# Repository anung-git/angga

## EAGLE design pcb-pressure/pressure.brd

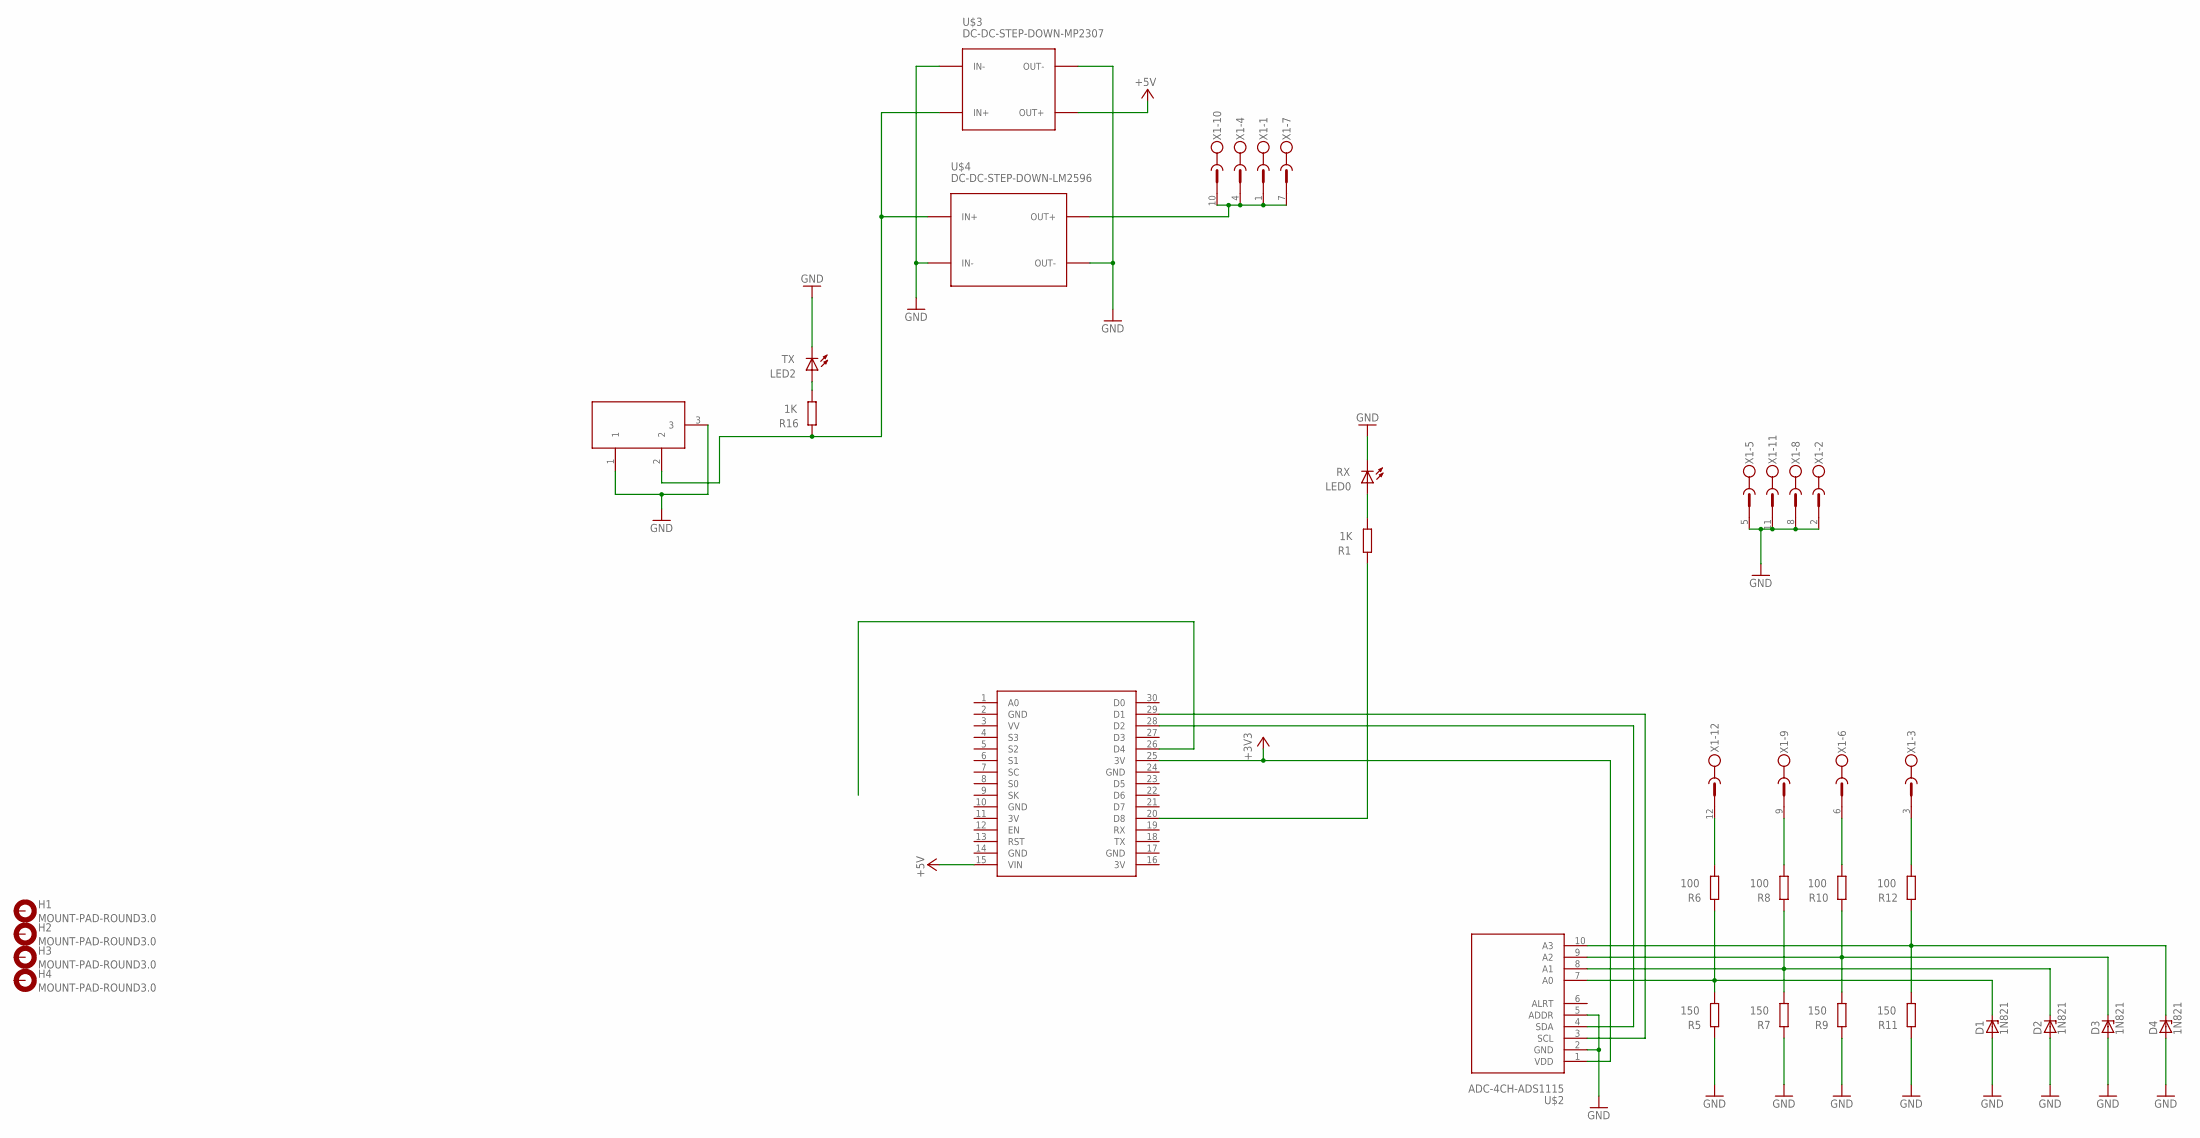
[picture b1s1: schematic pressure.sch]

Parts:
D1, D2, D3, D4: 1N821; DO35Z10
DC1: DC21MMX; DC-21MM
H1, H2, H3, H4: MOUNT-PAD-ROUND3.0; 3,0-PAD
LED0: RX; LED5MM
LED2: TX; LED5MM
R1, R16: 1K; 0207/10
R5, R7, R9, R11: 150; 0207/10
R6, R8, R10, R12: 100; 0207/10
U$1: NODEMCU
U$2: ADC-4CH-ADS1115
U$3: DC-DC-STEP-DOWN-MP2307
U$4: DC-DC-STEP-DOWN-LM2596
X1: MSTBV12

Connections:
3V: U$1.11 (3V), U$1.16 (3V)
+3V3: U$1.25 (3V), U$2.1 (VDD)
+5V: U$1.15 (VIN), U$3.OUT+
GND: D1.A, D2.A, D3.A, D4.A, DC1.1, DC1.3, LED0.K (C), LED2.K (C), R5.2, R7.2, R9.2, R11.2, U$1.2 (GND), U$1.10 (GND), U$1.14 (GND), U$1.17 (GND), U$1.24 (GND), U$2.2 (GND), U$2.5 (ADDR), U$3.IN-, U$3.OUT-, U$4.IN-, U$4.OUT-, X1.2, X1.5, X1.8, X1.11
unnamed: DC1.2, R16.2, U$3.IN+, U$4.IN+
unnamed: U$4.OUT+, X1.1, X1.4, X1.7, X1.10
unnamed: D1.C, R5.1, R6.2, U$2.7 (A0)
unnamed: D2.C, R7.1, R8.2, U$2.8 (A1)
unnamed: D3.C, R9.1, R10.2, U$2.9 (A2)
unnamed: R1.2, U$1.20 (D8)
unnamed: D4.C, R11.1, R12.2, U$2.10 (A3)
unnamed: R6.1, X1.12
unnamed: R8.1, X1.9
unnamed: R10.1, X1.6
unnamed: LED2.A, R16.1
unnamed: R12.1, X1.3
unnamed: U$1.29 (D1), U$2.3 (SCL)
unnamed: U$1.28 (D2), U$2.4 (SDA)
unnamed: LED0.A, R1.1

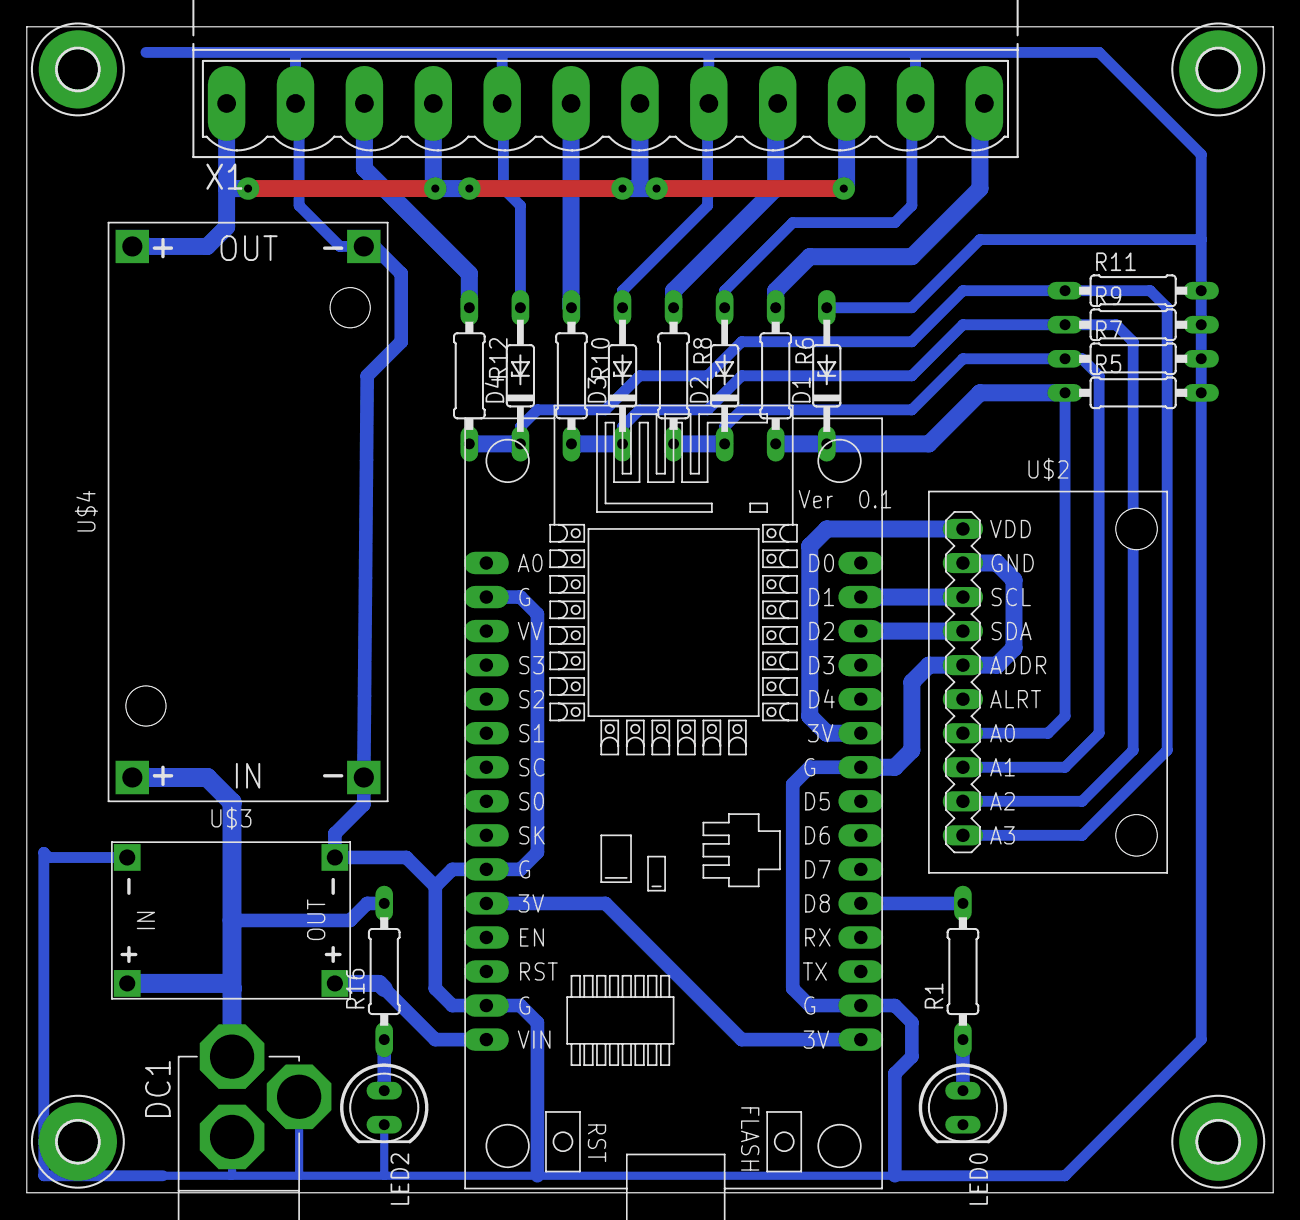
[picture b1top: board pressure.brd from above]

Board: 2 copper layers, 93.0 x 87.0 mm, 26 parts (0 on the bottom side), 19 nets.

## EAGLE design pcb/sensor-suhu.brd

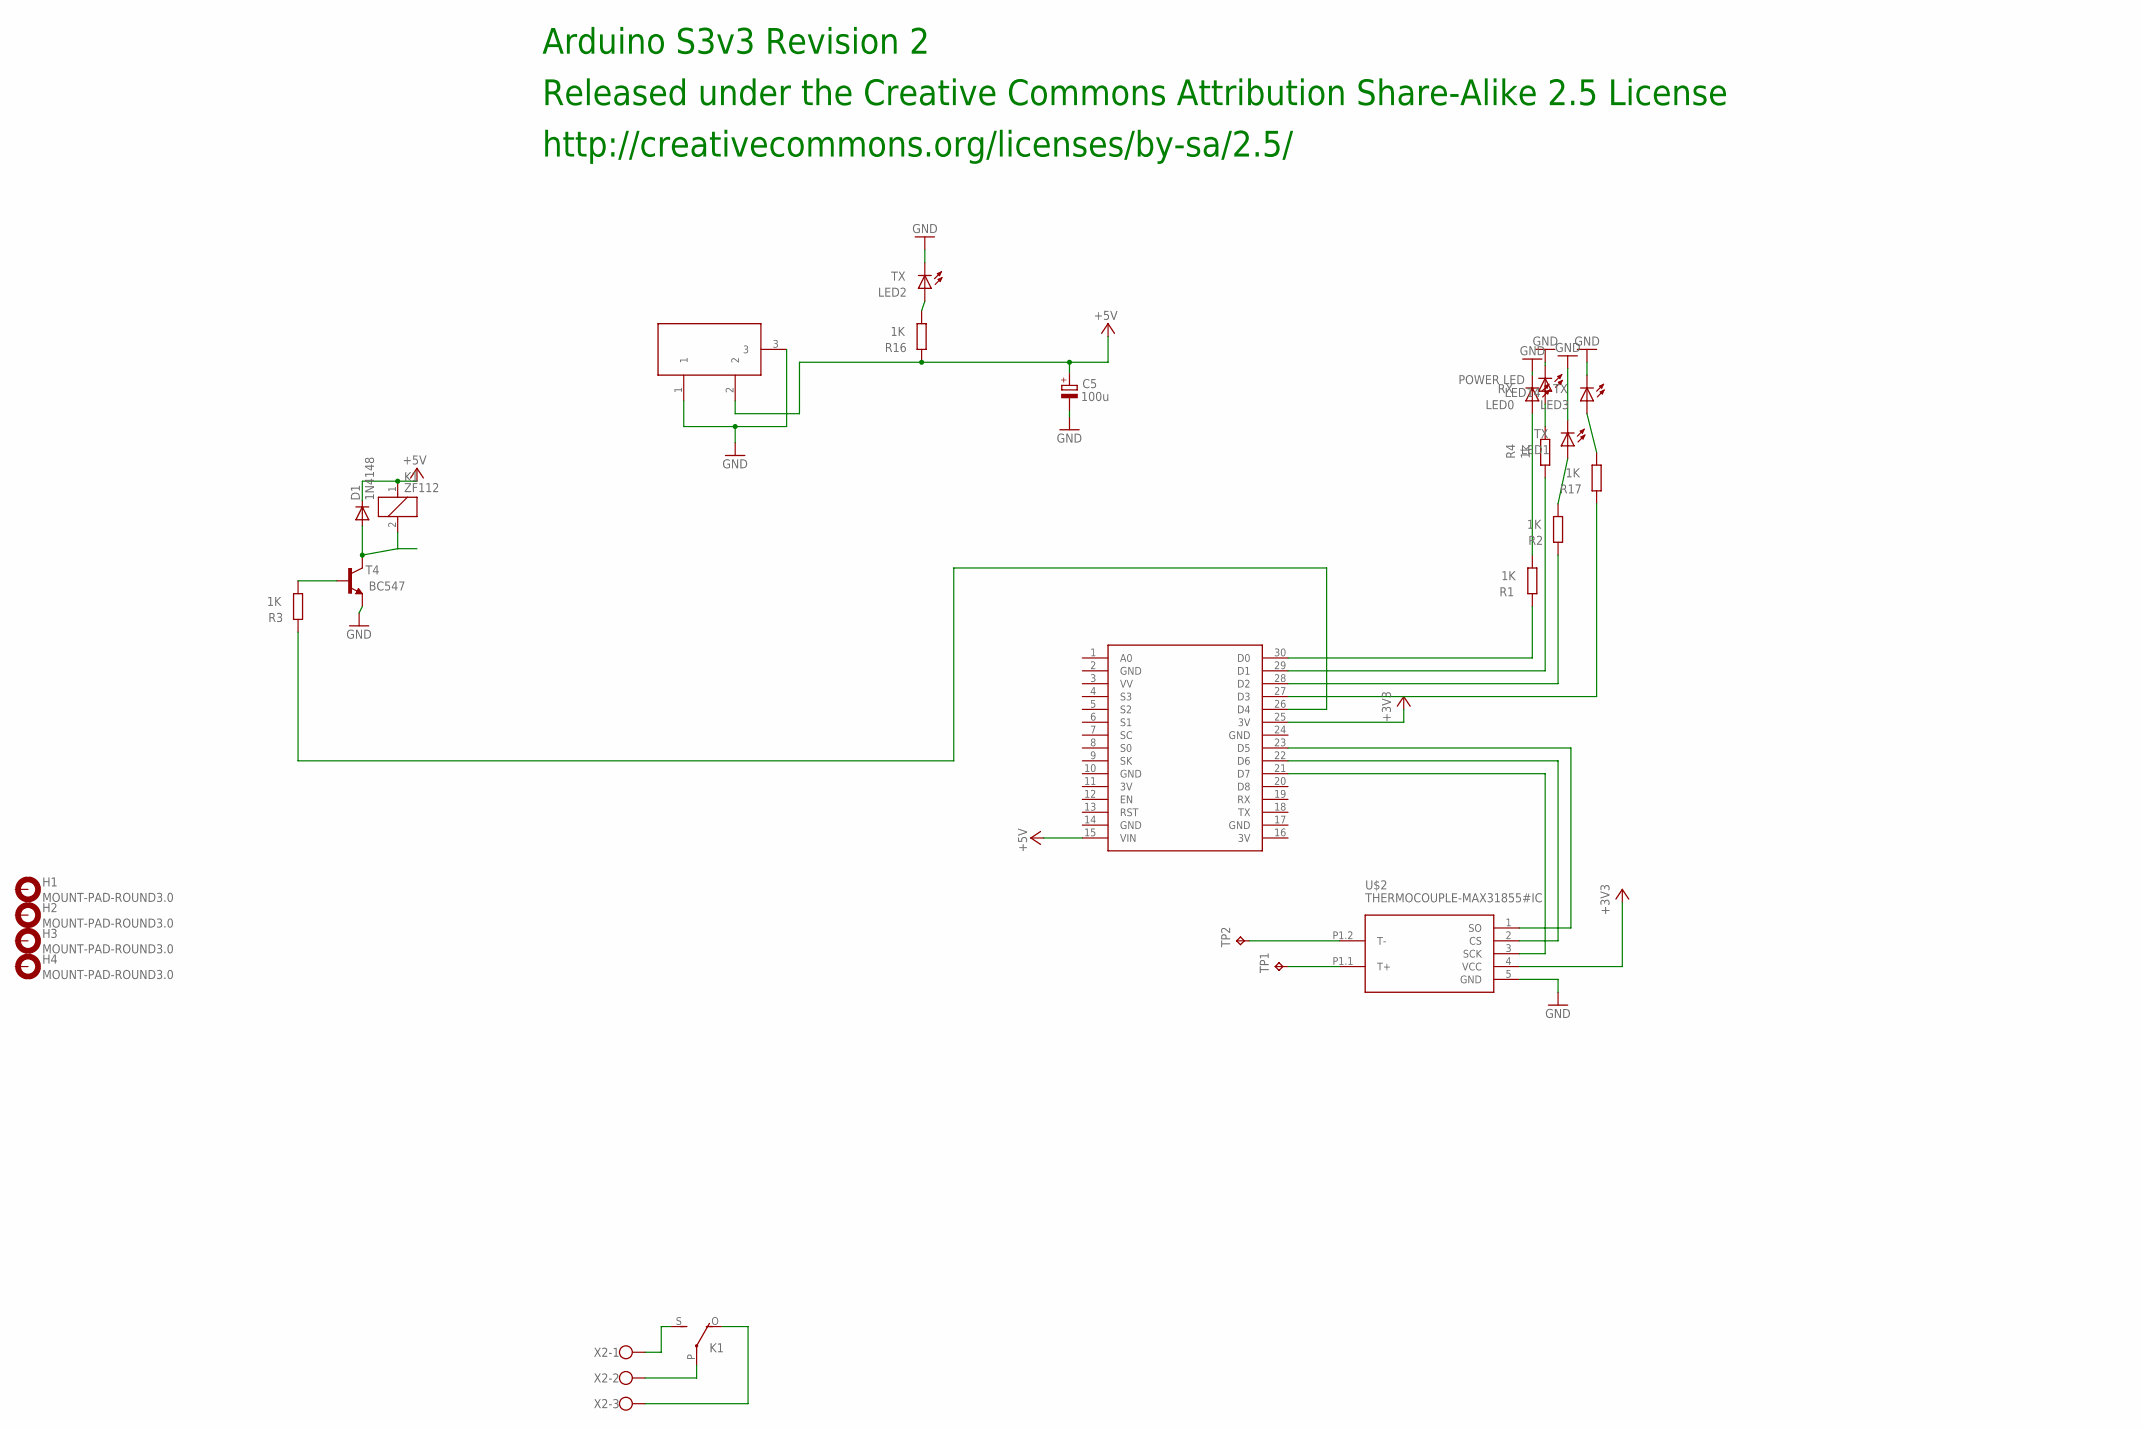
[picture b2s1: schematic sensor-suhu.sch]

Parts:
C5: 100u; E3,5-8
D1: 1N4148; DO35-10
DC1: DC21MMX; DC-21MM
H1, H2, H3, H4: MOUNT-PAD-ROUND3.0; 3,0-PAD
K1: ZF112
LED0: RX; LED5MM
LED1, LED2, LED3: TX; LED5MM
LED14: POWER LED; LED5MM
R1, R2, R3, R16, R17: 1K; 0207/10
R4: 1k; 0207/10
T4: BC547; TO92
TP1, TP2: TPPAD1-17Y; P1-17Y
U$1: NODEMCU
U$2: THERMOCOUPLE-MAX31855#IC
X2: W237-103

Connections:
3V: U$1.11 (3V), U$1.16 (3V)
+3V3: U$1.25 (3V), U$2.4 (VCC)
+5V: C5.+, D1.C, DC1.2, K1.1, R16.2, U$1.15 (VIN)
GND: C5.-, DC1.1, DC1.3, LED0.K (C), LED1.K (C), LED2.K (C), LED3.K (C), LED14.K (C), T4.1 (E), U$1.2 (GND), U$1.10 (GND), U$1.14 (GND), U$1.17 (GND), U$1.24 (GND), U$2.5 (GND)
unnamed: R3.1, T4.2 (B)
unnamed: K1.O, X2.3
unnamed: LED14.A, R4.1
unnamed: D1.A, K1.2, T4.3 (C)
unnamed: U$1.23 (D5), U$2.1 (SO)
unnamed: U$1.22 (D6), U$2.2 (CS)
unnamed: U$1.21 (D7), U$2.3 (SCK)
unnamed: K1.S, X2.1
unnamed: K1.P, X2.2
unnamed: R1.2, U$1.30 (D0)
unnamed: R4.2, U$1.29 (D1)
unnamed: R2.2, U$1.28 (D2)
unnamed: R17.2, U$1.27 (D3)
unnamed: R3.2, U$1.26 (D4)
unnamed: TP2.TP, U$2.P1.2 (T-)
unnamed: TP1.TP, U$2.P1.1 (T+)
unnamed: LED2.A, R16.1
unnamed: LED3.A, R17.1
unnamed: LED1.A, R2.1
unnamed: LED0.A, R1.1

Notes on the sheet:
Released under the Creative Commons Attribution Share-Alike 2.5 License
http://creativecommons.org/licenses/by-sa/2.5/
Arduino S3v3 Revision 2

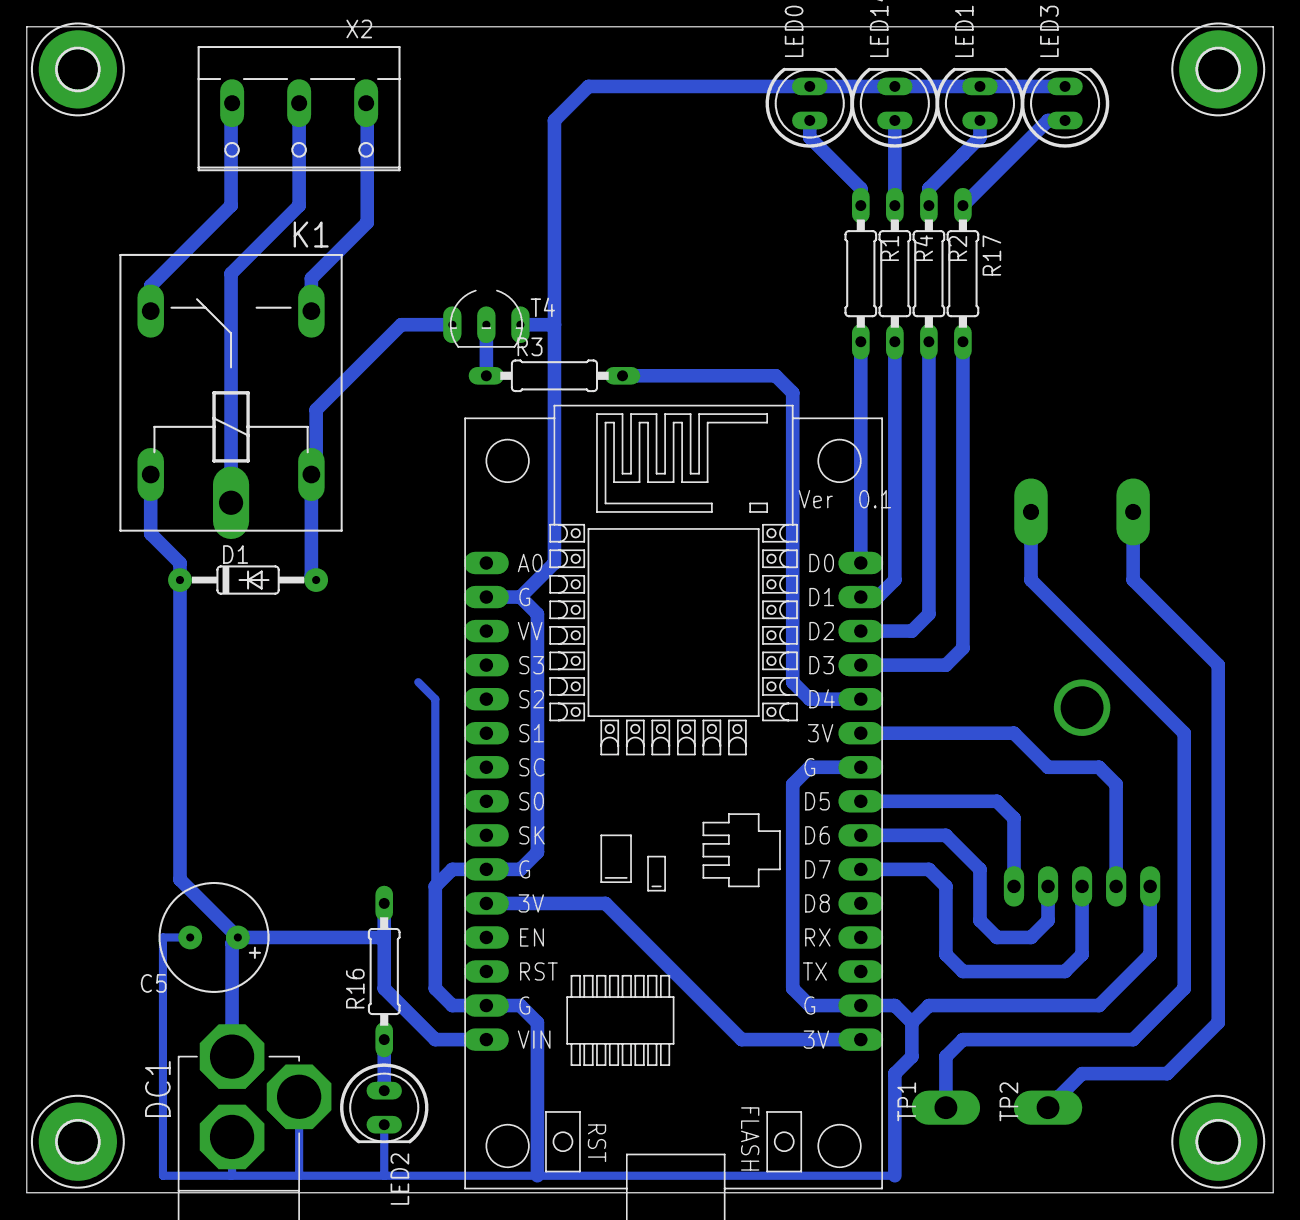
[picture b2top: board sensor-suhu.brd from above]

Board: 2 copper layers, 93.0 x 87.0 mm, 25 parts (1 on the bottom side), 24 nets.

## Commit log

2020-04-06 upload file
2020-04-26 harga
2020-05-19 pressure pcb
2020-05-27 update v1
2020-06-04 tekanan

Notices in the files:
parts and their libraries:
diy-modules: Released under the Creative Commons Attribution 4.0 International License: http://creativecommons.org/licenses/by/4.0
